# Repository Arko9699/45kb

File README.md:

# ark40
A simple 40% keyboard with an HHKB-like layout. Two-piece case with gasket mounting, inspired by the flurpes' .

# Layout

# Renders

# Features
* HHKB-like layout
* Gasket mount
* 
* QMK Firmware (WIP)
* Made using KiCad 7.0.5

# Specs
* Front Height : 19mm
* Dimensions : 285.2mm x 92mm x 26.9mm
* Typing Angle : 4.5 degree
* Case Material : Aluminium 6061
* Case Weight : 782g
* Gaskets : 8x rounded 60mm x 4mm x 3mm gasket strips (compatible with D65 gasket strips on KBDFans)
# NOTE
There is an case bottom that is meant to be used with a Waveshare RP2040 Zero for a handwired build. Make sure to use the correct plate file with plate mount stabilisers cutouts.

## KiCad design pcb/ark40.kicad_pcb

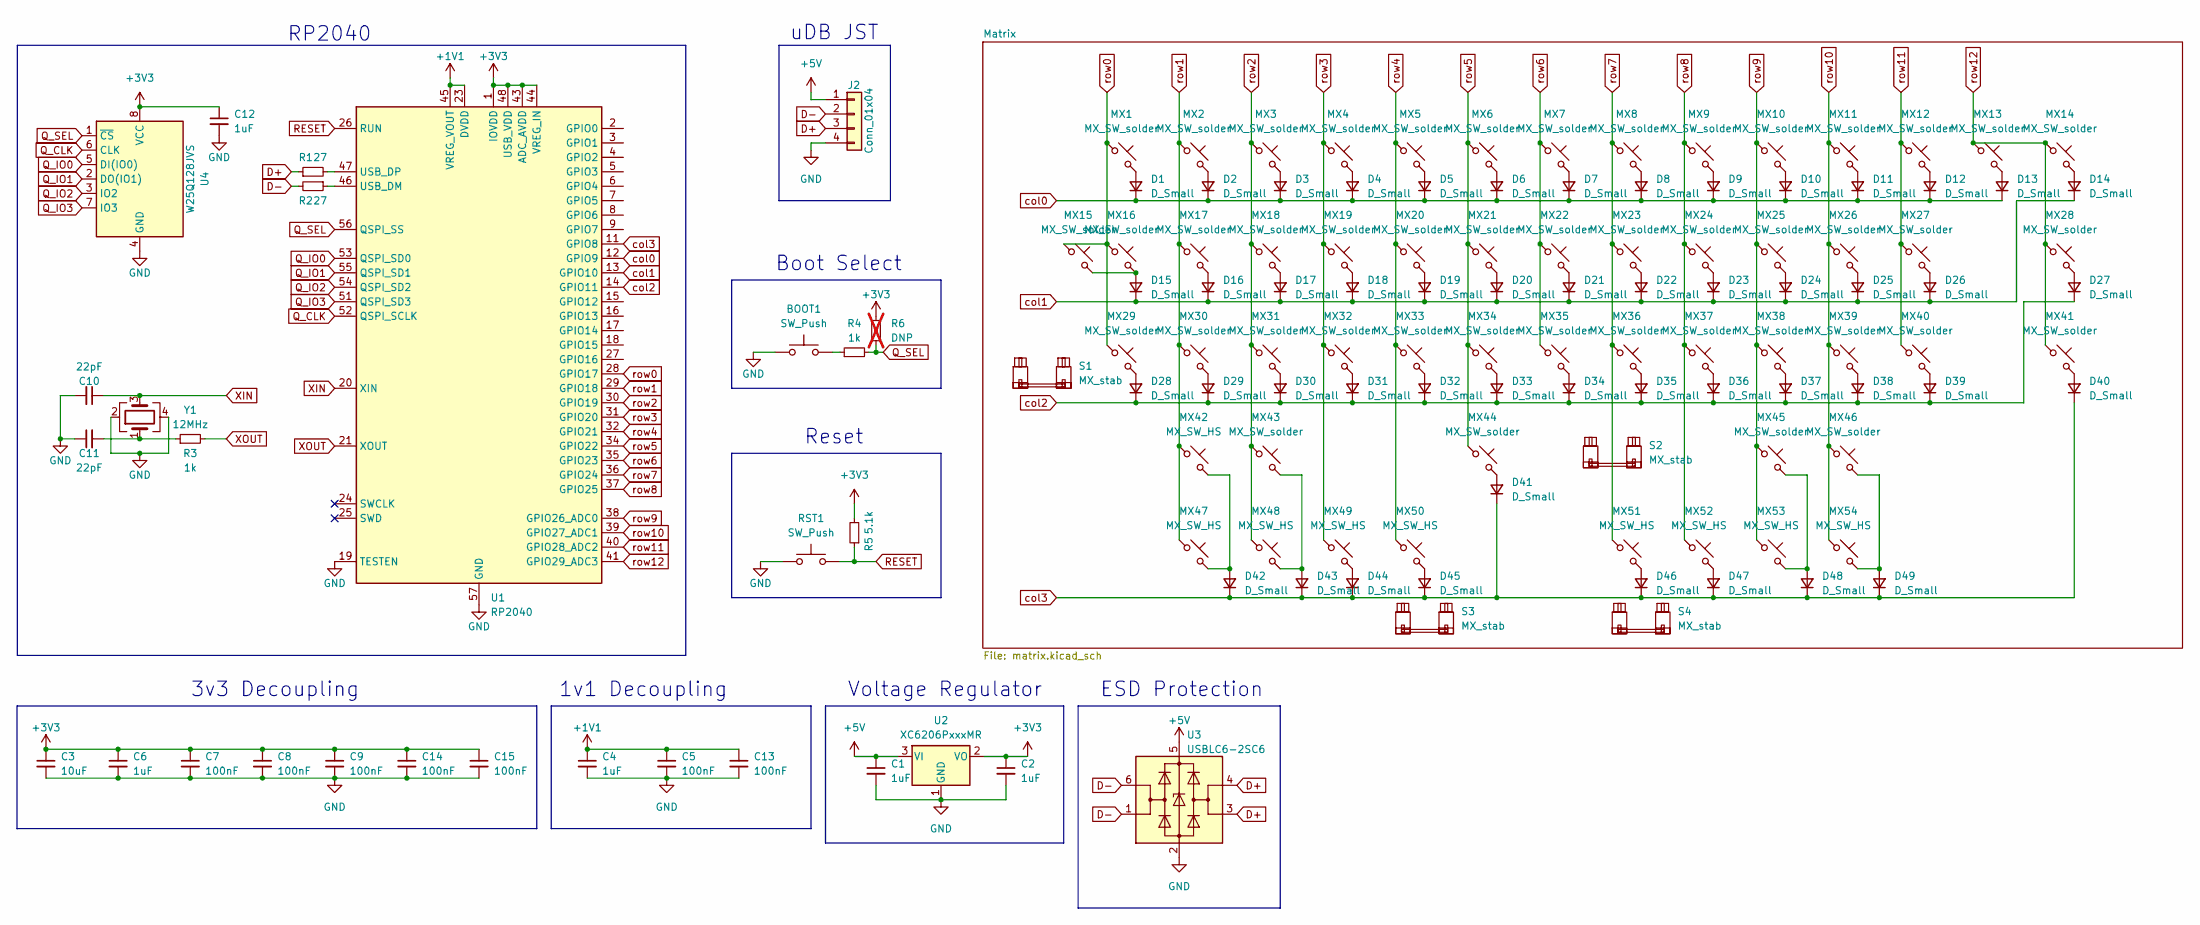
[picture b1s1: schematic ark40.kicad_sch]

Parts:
BOOT1: SW_Push; SW_SPST_TL3342; LCSC C318884
C1, C2, C4, C6, C12: 1uF; C_0402_1005Metric; LCSC C52923
C3: 10uF; C_0603_1608Metric; LCSC C19702
C5, C7, C8, C9, C13, C14, C15: 100nF; C_0402_1005Metric; LCSC C1525
C10, C11: 22pF; C_0402_1005Metric; LCSC C1555
D1, D2, D3, D4, D5, D6, D7, D8, D9, D10, D11, D12, D13, D14, D15, D16, D17, D18, D19, D20, D21, D22, D23, D24, D25, D26, D27, D28, D29, D30, D31, D32, D33, D34, D35, D36, D37, D38, D39, D40, D41, D42, D43, D44, D45, D46, D47, D48, D49: D_Small; D_SOD-123; LCSC C81598
J2: Conn_01x04; JST_SH_SM04B-SRSS-TB_1x04-1MP_P1.00mm_Horizontal; LCSC C160390
MX1, MX46: MX_SW_solder; SW_MX_1.5u
MX2, MX3, MX4, MX5, MX6, MX7, MX8, MX9, MX10, MX11, MX12, MX13, MX14, MX17, MX18, MX19, MX20, MX21, MX22, MX23, MX24, MX25, MX26, MX27, MX29, MX30, MX31, MX32, MX33, MX34, MX35, MX36, MX37, MX38, MX39, MX41, MX44: MX_SW_solder; SW_MX_1u
MX15, MX28: MX_SW_solder; SW_MX_1.75u
MX16: MX_SW_solder; SW_MX_1.75u_STP_1.25
MX40, MX43, MX45: MX_SW_solder; SW_MX_1.25u
MX42: MX_SW_HS; SW_MX_1.5u
MX47, MX54: MX_SW_HS; SW_MX_1.25u
MX48, MX49, MX50, MX51, MX52, MX53: MX_SW_HS; SW_MX_1u
R1, R2: 27; R_0402_1005Metric; LCSC C140174
R3, R4: 1k; R_0402_1005Metric; LCSC C11702
R5: 5.1k; R_0402_1005Metric; LCSC C25905
R6: DNP; R_0402_1005Metric; LCSC C279981; not fitted
RST1: SW_Push; SW_SPST_TL3342; LCSC C318884
S1, S3: MX_stab; STAB_MX_P_2.25u
S2: MX_stab; STAB_MX_P_6u
S4: MX_stab; STAB_MX_P_2.75u
U1: RP2040; QFN-56-1EP_7x7mm_P0.4mm_EP3.2x3.2mm; LCSC C2040
U2: XC6206PxxxMR; SOT-23-3; LCSC C5446
U3: USBLC6-2SC6; SOT-23-6; LCSC C2687116
U4: W25Q128JVS; SOIC-8_5.23x5.23mm_P1.27mm; LCSC C97521
Y1: 12MHz; Crystal_SMD_3225-4Pin_3.2x2.5mm; LCSC C9002

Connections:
+1V1: C4.1, C5.1, C13.1, U1.23 (DVDD), U1.45 (VREG_VOUT), U1.50 (DVDD)
+3V3: C2.1, C3.1, C6.1, C7.1, C8.1, C9.1, C12.1, C14.1, C15.1, R5.2, R6.2, U1.1 (IOVDD), U1.10 (IOVDD), U1.22 (IOVDD), U1.33 (IOVDD), U1.42 (IOVDD), U1.43 (ADC_AVDD), U1.44 (VREG_IN), U1.48 (USB_VDD), U1.49 (IOVDD), U2.2 (VO), U4.8 (VCC)
+5V: C1.1, J2.1, U2.3 (VI), U3.5 (VBUS)
D+: J2.3, R1.1, U3.3 (I/O2), U3.4 (I/O2)
D-: J2.2, R2.2, U3.1 (I/O1), U3.6 (I/O1)
GND: BOOT1.1, C1.2, C2.2, C3.2, C4.2, C5.2, C6.2, C7.2, C8.2, C9.2, C10.2, C11.1, C12.2, C13.2, C14.2, C15.2, J2.4, RST1.1, U1.19 (TESTEN), U1.57 (GND), U2.1 (GND), U3.2 (GND), U4.4 (GND), Y1.2, Y1.4
unnamed: BOOT1.2, R4.1
unnamed: C11.2, R3.1, Y1.1
unnamed: D1.2 (A), MX1.2
unnamed: D2.2 (A), MX2.2
unnamed: D3.2 (A), MX3.2
unnamed: D4.2 (A), MX4.2
unnamed: D5.2 (A), MX5.2
unnamed: D6.2 (A), MX6.2
unnamed: D7.2 (A), MX7.2
unnamed: D8.2 (A), MX8.2
unnamed: D9.2 (A), MX9.2
unnamed: D10.2 (A), MX10.2
unnamed: D11.2 (A), MX11.2
unnamed: D12.2 (A), MX12.2
unnamed: D13.2 (A), MX13.2
unnamed: D14.2 (A), MX14.2
unnamed: D15.2 (A), MX15.2, MX16.2
unnamed: D16.2 (A), MX17.2
unnamed: D17.2 (A), MX18.2
unnamed: D18.2 (A), MX19.2
unnamed: D19.2 (A), MX20.2
unnamed: D20.2 (A), MX21.2
unnamed: D21.2 (A), MX22.2
unnamed: D22.2 (A), MX23.2
unnamed: D23.2 (A), MX24.2
unnamed: D24.2 (A), MX25.2
unnamed: D25.2 (A), MX26.2
unnamed: D26.2 (A), MX27.2
unnamed: D27.2 (A), MX28.2
unnamed: D28.2 (A), MX29.2
unnamed: D29.2 (A), MX30.2
unnamed: D30.2 (A), MX31.2
unnamed: D31.2 (A), MX32.2
unnamed: D32.2 (A), MX33.2
unnamed: D33.2 (A), MX34.2
unnamed: D34.2 (A), MX35.2
unnamed: D35.2 (A), MX36.2
unnamed: D36.2 (A), MX37.2
unnamed: D37.2 (A), MX38.2
unnamed: D38.2 (A), MX39.2
unnamed: D39.2 (A), MX40.2
unnamed: D40.2 (A), MX41.2
unnamed: D41.2 (A), MX44.2
unnamed: D42.2 (A), MX42.2, MX47.2
unnamed: D43.2 (A), MX43.2, MX48.2
unnamed: D44.2 (A), MX49.2
unnamed: D45.2 (A), MX50.2
unnamed: D46.2 (A), MX51.2
unnamed: D47.2 (A), MX52.2
unnamed: D48.2 (A), MX45.2, MX53.2
unnamed: D49.2 (A), MX46.2, MX54.2
unnamed: R2.1, U1.46 (USB_DM)
unnamed: R1.2, U1.47 (USB_DP)
Q_CLK: U1.52 (QSPI_SCLK), U4.6 (CLK)
Q_IO0: U1.53 (QSPI_SD0), U4.5 (DI(IO0))
Q_IO1: U1.55 (QSPI_SD1), U4.2 (DO(IO1))
Q_IO2: U1.54 (QSPI_SD2), U4.3 (IO2)
Q_IO3: U1.51 (QSPI_SD3), U4.7 (IO3)
Q_SEL: R4.2, R6.1, U1.56 (QSPI_SS), U4.1 (~CS)
RESET: R5.1, RST1.2, U1.26 (RUN)
XIN: C10.1, U1.20 (XIN), Y1.3
XOUT: R3.2, U1.21 (XOUT)
col0: D1.1 (K), D2.1 (K), D3.1 (K), D4.1 (K), D5.1 (K), D6.1 (K), D7.1 (K), D8.1 (K), D9.1 (K), D10.1 (K), D11.1 (K), D12.1 (K), D13.1 (K), U1.12 (GPIO9)
col1: D14.1 (K), D15.1 (K), D16.1 (K), D17.1 (K), D18.1 (K), D19.1 (K), D20.1 (K), D21.1 (K), D22.1 (K), D23.1 (K), D24.1 (K), D25.1 (K), D26.1 (K), U1.13 (GPIO10)
col2: D27.1 (K), D28.1 (K), D29.1 (K), D30.1 (K), D31.1 (K), D32.1 (K), D33.1 (K), D34.1 (K), D35.1 (K), D36.1 (K), D37.1 (K), D38.1 (K), D39.1 (K), U1.14 (GPIO11)
col3: D40.1 (K), D41.1 (K), D42.1 (K), D43.1 (K), D44.1 (K), D45.1 (K), D46.1 (K), D47.1 (K), D48.1 (K), D49.1 (K), U1.11 (GPIO8)
row0: MX1.1, MX15.1, MX16.1, MX29.1, U1.28 (GPIO17)
row1: MX2.1, MX17.1, MX30.1, MX42.1, MX47.1, U1.29 (GPIO18)
row2: MX3.1, MX18.1, MX31.1, MX43.1, MX48.1, U1.30 (GPIO19)
row3: MX4.1, MX19.1, MX32.1, MX49.1, U1.31 (GPIO20)
row4: MX5.1, MX20.1, MX33.1, MX50.1, U1.32 (GPIO21)
row5: MX6.1, MX21.1, MX34.1, MX44.1, U1.34 (GPIO22)
row6: MX7.1, MX22.1, MX35.1, U1.35 (GPIO23)
row7: MX8.1, MX23.1, MX36.1, MX51.1, U1.36 (GPIO24)
row8: MX9.1, MX24.1, MX37.1, MX52.1, U1.37 (GPIO25)
row9: MX10.1, MX25.1, MX38.1, MX45.1, MX53.1, U1.38 (GPIO26_ADC0)
row10: MX11.1, MX26.1, MX39.1, MX46.1, MX54.1, U1.39 (GPIO27_ADC1)
row11: MX12.1, MX27.1, MX40.1, U1.40 (GPIO28_ADC2)
row12: MX13.1, MX14.1, MX28.1, MX41.1, U1.41 (GPIO29_ADC3)

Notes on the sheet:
uDB JST
1v1 Decoupling
Reset
3v3 Decoupling
Boot Select
RP2040
Voltage Regulator
ESD Protection

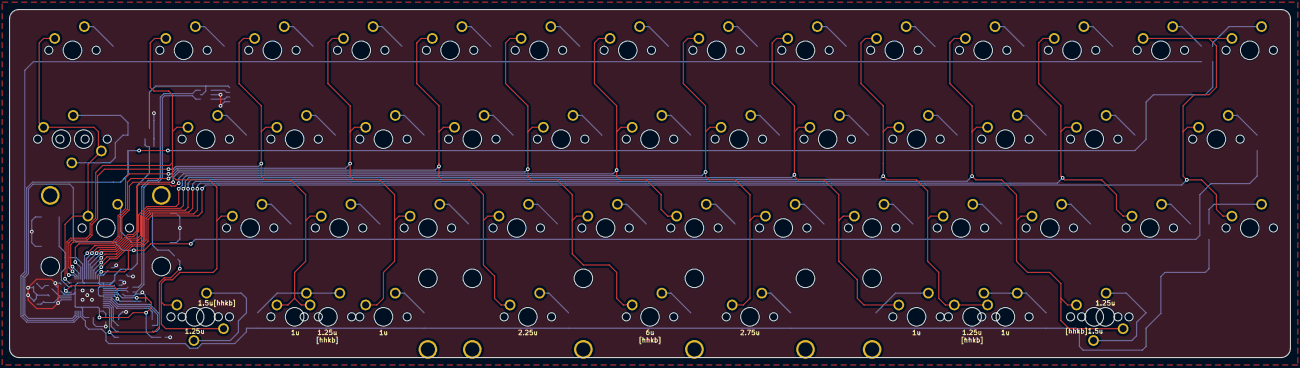
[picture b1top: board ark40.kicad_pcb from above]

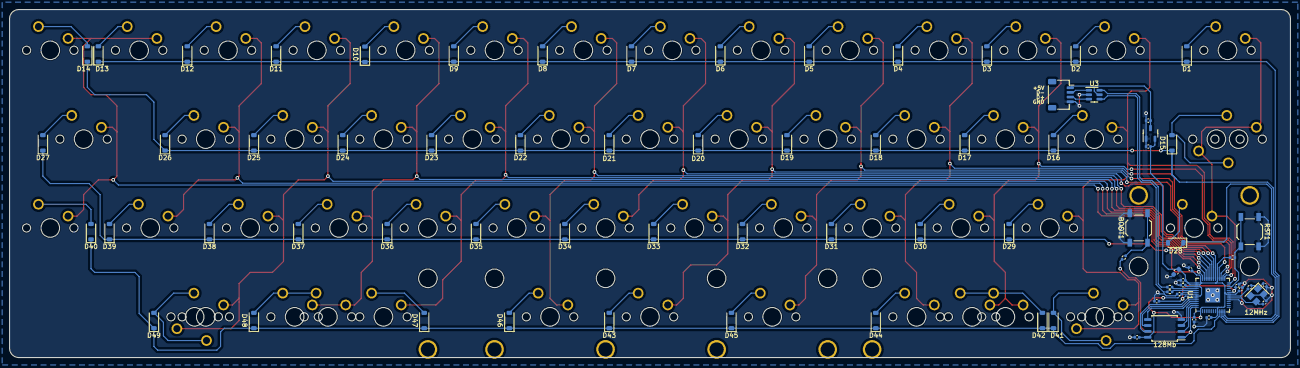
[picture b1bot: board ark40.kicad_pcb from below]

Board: 2 copper layers, 274.6 x 74.6 mm, 135 parts (77 on the bottom side), 85 nets.

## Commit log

2023-05-16 plate file to get it in other materials
2023-07-06 Added pics
